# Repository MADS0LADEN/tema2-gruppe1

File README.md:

# tema2-gruppe1

Rover

## TODO

### Control Protocol

Der skal laves en ny løsning som gør at vi kan styre begge motor i samme pakke

Der sendes beskeder til roveren via UDP på denne måde:

- "STOP"                    = "0"
- "Ligeud"                  = "100 100"
- "Bagud"                   = "-100 -100"
- "Ligeud lidt til højre"   = "100 80"
- "Ligeud lidt til venstre" = "80 100"
Første tal er venstre og andet er højre hjul

### Frontend / Client

Hjemmesiden til at sende styre input til roveren

##### Knapper

Fedest hvis vi kan få tastatur knapperne til at virke.
Ellers kan vi lave joysticks på hjemmesiden som man kunne styre fra en touchskærm

##### CLI Client

Hvis det er nemmere kan vi også se om vi kan lave et program der køres i console til at tage imod input fra tastaturet

### Backend / Server

Dette er koden som skal styre rover samt modtage kommandoer fra hjemmesiden man bruger som controller

##### Netværk

Finde en løsning til at modtage beskeder fra klienten som kan konverteres til styring af rover

##### Styring af motor

Finde en optimal løsning til at få roveren til at gøre som vi beder den om (køre ligeud hvis vi vil det)

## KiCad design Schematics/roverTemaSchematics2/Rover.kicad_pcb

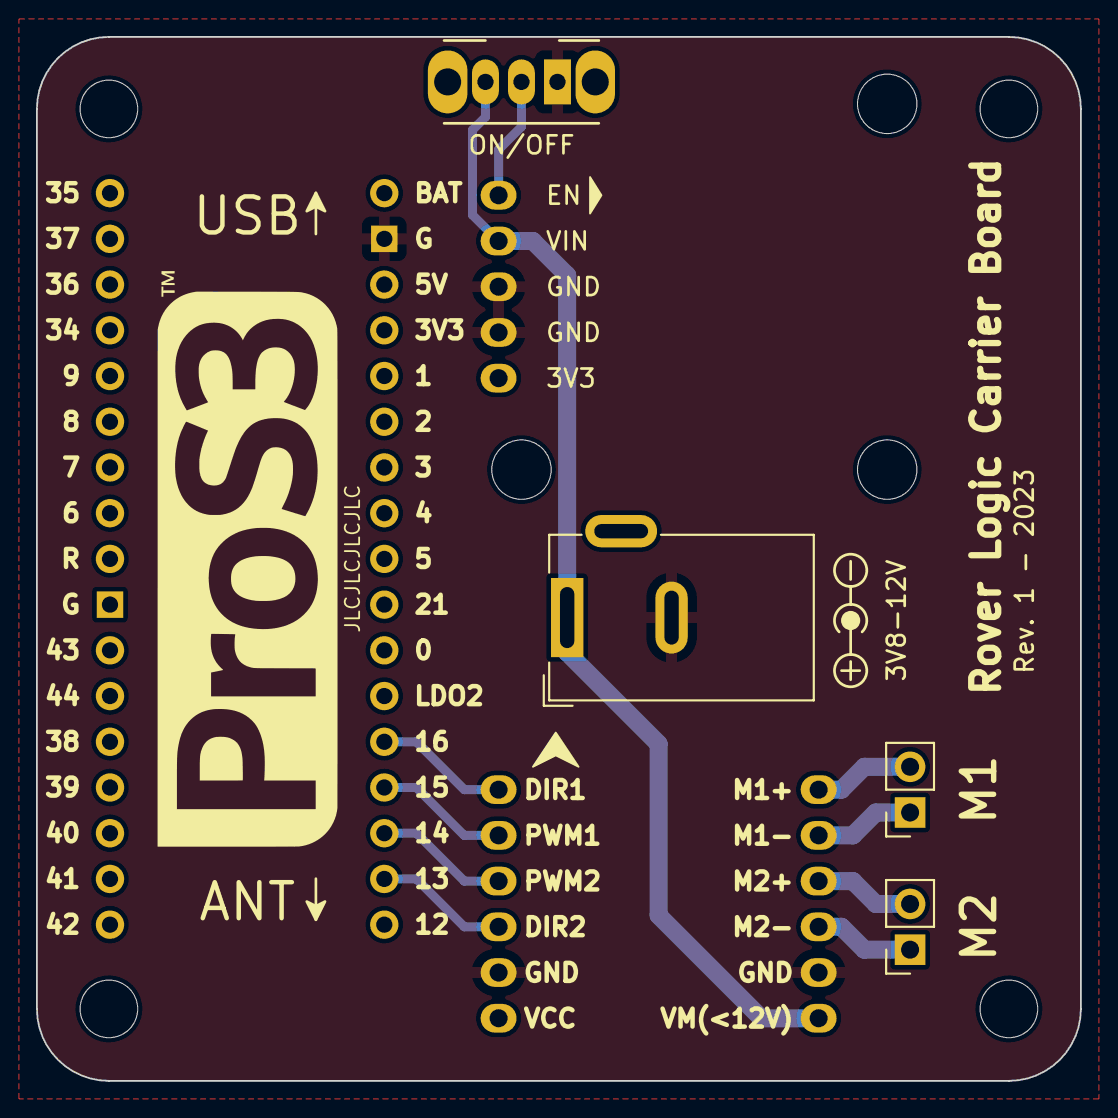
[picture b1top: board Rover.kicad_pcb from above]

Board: 2 copper layers, 58.0 x 58.0 mm, 11 parts (0 on the bottom side), 12 nets.

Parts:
H1, H2, H3, H4: MountingHole; MountingHole_3.2mm_M3_ISO7380
J1: Barrel_Jack; BarrelJack_Wuerth_6941xx301002
J2, J3: Conn_01x02_Socket; PinSocket_1x02_P2.54mm_Vertical
SW1: SW_SPDT; SW_CuK_OS102011MA1QN1_SPDT_Angled
U1: ProS3; ProS3_TH
U2: Buck Regulator; AP63203 Sparkfun Buck Regulator module - upside-down
U3: Motordriver; TB6612FNG DfRobot motordriver module

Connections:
/3V3: U1.4 (3V3), U2.1 (3v3), U3.6 (VCC)
/DIR1: U1.13 (IO16), U3.1 (DIR1)
/DIR2: U1.16 (IO13), U3.4 (DIR2)
/GND: J1.2, SW1.1 (A), U1.2 (GND), U2.2 (GND), U2.3 (GND), U3.5 (GND), U3.8 (GND)
/PWM1: U1.14 (IO15), U3.2 (PWM1)
/PWM2: U1.15 (IO14), U3.3 (PWM2)
/VIN: J1.1, SW1.3 (C), U2.4 (VIN), U3.7 (VM)
unnamed: J2.1, U3.9 (M2-)
unnamed: J2.2, U3.10 (M2+)
unnamed: J3.1, U3.11 (M1-)
unnamed: J3.2, U3.12 (M1+)
unnamed: SW1.2 (B), U2.5 (EN)

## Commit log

2023-11-03 Update README.md
    Tilføjet todo liste
2023-11-03 udp + dev branch
2023-11-07 update readme og tilføj AP til esp udp
2023-11-07 remove test
2023-11-07 Update README.md
    fix formatting
2023-11-07 make udp server runnable on ESP and PC
2023-11-07 joystick.py and joystickStyrring er tilføjet til github mappen dev
2023-11-07 awesome stuff
2023-11-07 show ip of machine for debugging
2023-11-07 handle all types of packets
2023-11-07 handle exeptions and reduce the bytes needed
2023-11-07 multiplatform
2023-11-07 isnumeric not available on uPy
2023-11-07 flutter app init
2023-11-07 dont know
2023-11-08 add debugging
2023-11-08 catch errors
2023-11-08 added connect-to-wifi.py and joystikStryrring cahnge
    joystickStyrring.py can now connect to the udp server and send values
2023-11-08 fix typo and send default packet of 0 to stop
2023-11-08 files from rover
2023-11-10 add keyboardread.py
2023-11-10 updated driver.py and main.py
2023-11-13 updated joystick
2023-11-14 oprydning
2023-11-14 keyboard med pygame samt fix af pakke længde
2023-11-16 opdateret udp protocol
2023-11-16 begyndelse på trim
2023-11-17 formatting
2023-11-19 stuff
2023-11-20 potentiometer.py added
2023-11-20 updated potentiometer.py
2023-11-21 delay pis, fatter intet
2023-11-21 change turn rate
2023-11-21 update freq
2023-11-23 mulighed for at ændre frekvens fra controller
2023-11-23 changed controls
    changed the controls to directly translate to procent
2023-11-23 added a button
    added a button to enable it to drive in reverse
2023-11-23 tested on esp
2023-11-26 added schematics
    made a folder and added all the schematics for the projekt in it.
    Needs to be oppend in kicad
2023-11-29 changes to joystick.py
    made the joystick application able to run with the new driver
2023-12-05 add rc controller
2023-12-07 tilpasset 3d print
2023-12-07 added button
2023-12-07 update from rover esp
2023-12-07 added mappe til wiseflow
2023-12-07 rc schematic
2024-02-26 DET VIRKER!!!
